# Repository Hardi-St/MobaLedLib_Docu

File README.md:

# MobaLedLib
Arduino library for controlling LEDs and other components on a model railway.

*****************************************************************
  This repository contains the documentation for the MobaLedLib
*****************************************************************

The use of RGB LEDs offers fascinating possibilities for lighting a model railway:
- Infinite number of lighting effects - Brightness and color of each LED can be
  set individually and dynamically
- Easiest cabling - The objects (houses, traffic lights, ...) are simply plugged
  into a multiple socket
- Extremely affordable - 100 LEDs for the price of three "normal" lights
- Up to 256 RGB LEDs (768 channels) can be controlled by an Arduino
- Controlling other components is just as easy
  - Sound modules
  - Servo and stepper motors
  - Power devices
- Additional module to read 80 and more switches with 10 signal wires
- Stand-alone operation or networked with other components possible

The lighting and some additional functions are controlled via the WS2812 / WS2811 chips.
For this, only a single signal is required which is forwarded from one chip to the next.
This makes the wiring extremely easy.

A lot of examples show the usage of the library. They could be use as startup for own programs.

This library is described in detail here:\
  https://www.stummiforum.de/viewtopic.php?f=7&t=165060&sid=e3b7f6122766c330d04cecf18b7b4878 \
Several videos which demonstrate the library are available in the following pages in the forum.

All forum pages are also available as PDF document:\
  http://www.thkas-moba.de/mobaled/MoBaLED_Stummi_Komplette_Seiten.pdf \
(The most recent pages may not be included)

Our wiki with all information can be found here: https://wiki.mobaledlib.de

You could also search for MobaLedLib in the internet.
\
\
Questions / suggestions / praise / ...
  MobaLedLib@gmx.de

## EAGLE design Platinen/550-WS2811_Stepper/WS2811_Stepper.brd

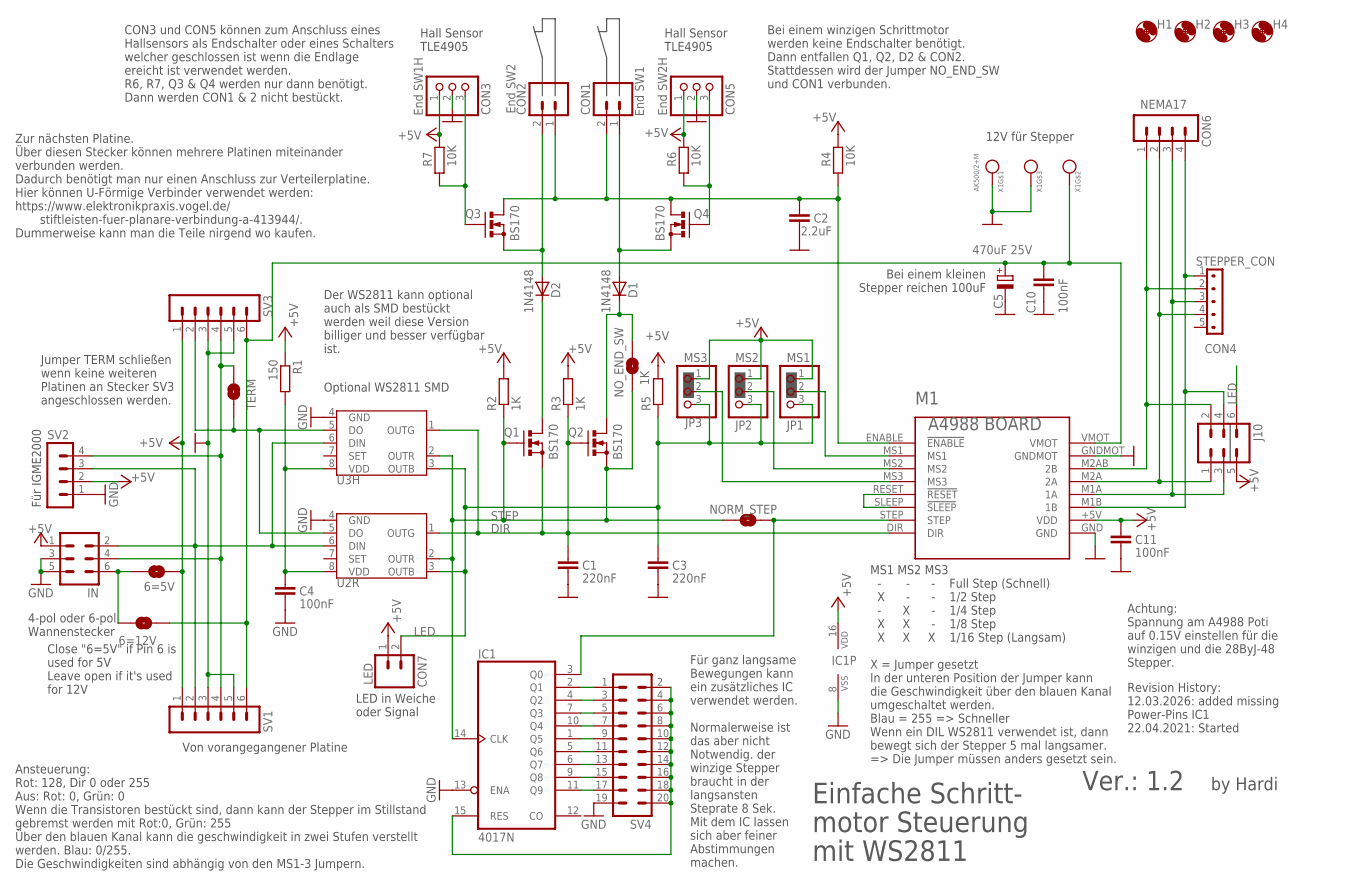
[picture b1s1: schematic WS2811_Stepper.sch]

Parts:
6=5V, 6=12V: SOLDERJUMPERNO; SJ_2S-NO
C1, C3: 220nF; C050-024X044
C2: 2.2uF; C050-024X044
C4, C10, C11: 100nF; C050-024X044
C5: 470uF 25V; E5-10,5
CON1: End SW1; 1X02
CON2: End SW2; 1X02
CON3: End SW1H; 1X03-CLEANBIG
CON4: STEPPER_CON
CON5: End SW2H; 1X03-CLEANBIG
CON6: NEMA17; MA04-1
CON7: LED; 1X02
D1, D2: 1N4148; DO35-7
H1, H2, H3, H4: MOUNT-HOLE2.0; 2,0
IC1: 4017N; DIL16
IN: ML6
J10: ML6
JP1: MS1; 1X03-CLEANBIG
JP2: MS2; 1X03-CLEANBIG
JP3: MS3; 1X03-CLEANBIG
M1: BOARD_A4988
NORM_STEP: SOLDERJUMPERNO; SJ_2S-NO
NO_END_SW: SOLDERJUMPERNO; SJ_2S-NO
Q1, Q2, Q3, Q4: BS170; SOT54E
R1: 150; RCL_0204/7
R2, R3, R5: 1K; RCL_0204/7
R4, R6, R7: 10K; RCL_0204/7
SV1, SV3: MA06-1
SV2: MA04-1
SV4: MA10-2
TERM: SOLDERJUMPERNO; SJ_2S-NO
U2R: WS2811; S3PO_MODUL_WS2811_SOUND_MP3-TF-16P_WS2811_AND_ATTINY_WS2811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
U3H: WS2811 SOT-8; SOP8
X1: AK500/2+M

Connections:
+5V: 6=5V.2, C11.1, CON3.1, CON5.1, CON7.1, IC1.16 (VDD), IN.1, J10.5, JP1.1, JP2.1, JP3.1, M1.+5V (VDD), R1.1, R2.2, R3.2, R4.2, R5.2, R6.2, R7.2, SV1.1, SV2.2, SV3.1
DIR: C1.1, M1.DIR, Q1.S, Q2.G, R3.1, U2R.1 (OUTG), U3H.1 (OUTG)
GND: C1.2, C2.2, C3.2, C4.2, C5.-, C10.2, C11.2, CON3.2, CON5.2, IC1.8 (VSS), IC1.13 (ENA), IN.3, IN.5, M1.GND, M1.GNDMOT, SV1.3, SV1.5, SV2.1, SV3.3, SV3.5, SV4.19, U2R.4 (GND), U3H.4 (GND), X1.1, X1.M
LED: C3.1, CON7.2, J10.6, JP1.3, JP2.3, JP3.3, R5.1, U2R.3 (OUTB), U3H.3 (OUTB)
M1A: CON4.3, CON6.3, J10.3, M1.M1A (1A)
M1B: CON4.1, CON6.4, J10.4, M1.M1B (1B)
M2A: CON4.4, CON6.2, J10.1, M1.M2A (2A)
M2B: CON4.2, CON6.1, J10.2, M1.M2AB (2B)
unnamed: M1.RESET (!RESET), M1.SLEEP (!SLEEP)
unnamed: IN.2, SV1.2, SV2.3, U2R.6 (DIN), U3H.6 (DIN)
unnamed: SV3.2, TERM.2, U2R.5 (DO), U3H.5 (DO)
unnamed: IN.4, SV1.4, SV2.4, SV3.4, TERM.1
unnamed: C4.1, R1.2, U2R.8 (VDD), U3H.8 (VDD)
unnamed: C2.1, CON1.2, CON2.1, M1.ENABLE (!ENABLE), Q3.D, Q4.D, R4.1
unnamed: CON1.1, D1.A, Q4.S
unnamed: CON2.2, D2.A, Q3.S
unnamed: CON5.3, Q4.G, R6.1
unnamed: D2.C, Q1.D
unnamed: D1.C, NO_END_SW.1, Q2.D
unnamed: JP2.2, M1.MS2
unnamed: 6=5V.1, 6=12V.2, IN.6
unnamed: CON3.3, Q3.G, R7.1
unnamed: IC1.2 (Q1), SV4.1
unnamed: IC1.4 (Q2), SV4.3
unnamed: IC1.7 (Q3), SV4.5
unnamed: IC1.10 (Q4), SV4.7
unnamed: JP1.2, M1.MS1
unnamed: IC1.1 (Q5), SV4.9
unnamed: IC1.5 (Q6), SV4.11
unnamed: IC1.6 (Q7), SV4.13
unnamed: IC1.9 (Q8), SV4.15
unnamed: JP3.2, M1.MS3
unnamed: IC1.11 (Q9), SV4.17
unnamed: IC1.15 (RES), SV4.2, SV4.4, SV4.6, SV4.8, SV4.10, SV4.12, SV4.14, SV4.16, SV4.18, SV4.20
unnamed: IC1.3 (Q0), M1.STEP, NORM_STEP.2
STEP: IC1.14 (CLK), NORM_STEP.1, NO_END_SW.2, Q1.G, Q2.S, R2.1, U2R.2 (OUTR), U3H.2 (OUTR)
VCC2: 6=12V.1, C5.+, C10.1, M1.VMOT, SV1.6, SV3.6, X1.2

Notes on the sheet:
4-pol oder 6-pol Wannenstecker
Close "6=5V" if Pin 6 is used for 5V Leave open if it's used for 12V
Optional WS2811 SMD
Zur nächsten Platine. Über diesen Stecker können mehrere Platinen miteinander verbunden werden. Dadurch benötigt man nur einen Anschluss zur Verteilerplatine. Hier können U-Förmige Verbinder verwendet werden: https://www.elektronikpraxis.vogel.de/ stiftleisten-fuer-planare-verbindung-a-413944/. Dum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
Von vorangegangener Platine
Der WS2811 kann optional auch als SMD bestückt werden weil diese Version billiger und besser verfügbar ist.
Jumper TERM schließen wenn keine weiteren Platinen an Stecker SV3 angeschlossen werden.
Revision History: 12.03.2026: added missing Power-Pins IC1 22.04.2021: Started
MS1 MS2 MS3 - - - Full Step (Schnell) X - - 1/2 Step - X - 1/4 Step X X - 1/8 Step X X X 1/16 Step (Langsam) X = Jumper gesetzt In der unteren Position der Jumper kann die Geschwindigkeit über den blauen Kanal umgeschaltet werden. Blau = 255 => Schneller Wenn ein DIL WS2811 verwendet ist, dann bewe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
12V für Stepper
by Hardi
Ver.: 1.2
Einfache Schritt- motor Steuerung mit WS2811
Bei einem winzigen Schrittmotor werden keine Endschalter benötigt. Dann entfallen Q1, Q2, D2 & CON2. Stattdessen wird der Jumper NO_END_SW und CON1 verbunden.
Achtung: Spannung am A4988 Poti auf 0.15V einstellen für die winzigen und die 28ByJ-48 Stepper.
Ansteuerung: Rot: 128, Dir 0 oder 255 Aus: Rot: 0, Grün: 0 Wenn die Transistoren bestückt sind, dann kann der Stepper im Stillstand gebremst werden mit Rot:0, Grün: 255 Über den blauen Kanal kann die geschwindigkeit in zwei Stufen verstellt werden. Blau: 0/255. Die Geschwindigkeiten sind abhängig v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
Hall Sensor TLE4905
CON3 und CON5 können zum Anschluss eines Hallsensors als Endschalter oder eines Schalters welcher geschlossen ist wenn die Endlage ereicht ist verwendet werden. R6, R7, Q3 & Q4 werden nur dann benötigt. Dann werden CON1 & 2 nicht bestückt.
Für IGME2000
Für ganz langsame Bewegungen kann ein zusätzliches IC verwendet werden. Normalerweise ist das aber nicht Notwendig. der winzige Stepper braucht in der langsansten Steprate 8 Sek. Mit dem IC lassen sich aber feiner Abstimmungen machen.
LED in Weiche oder Signal
Bei einem kleinen Stepper reichen 100uF

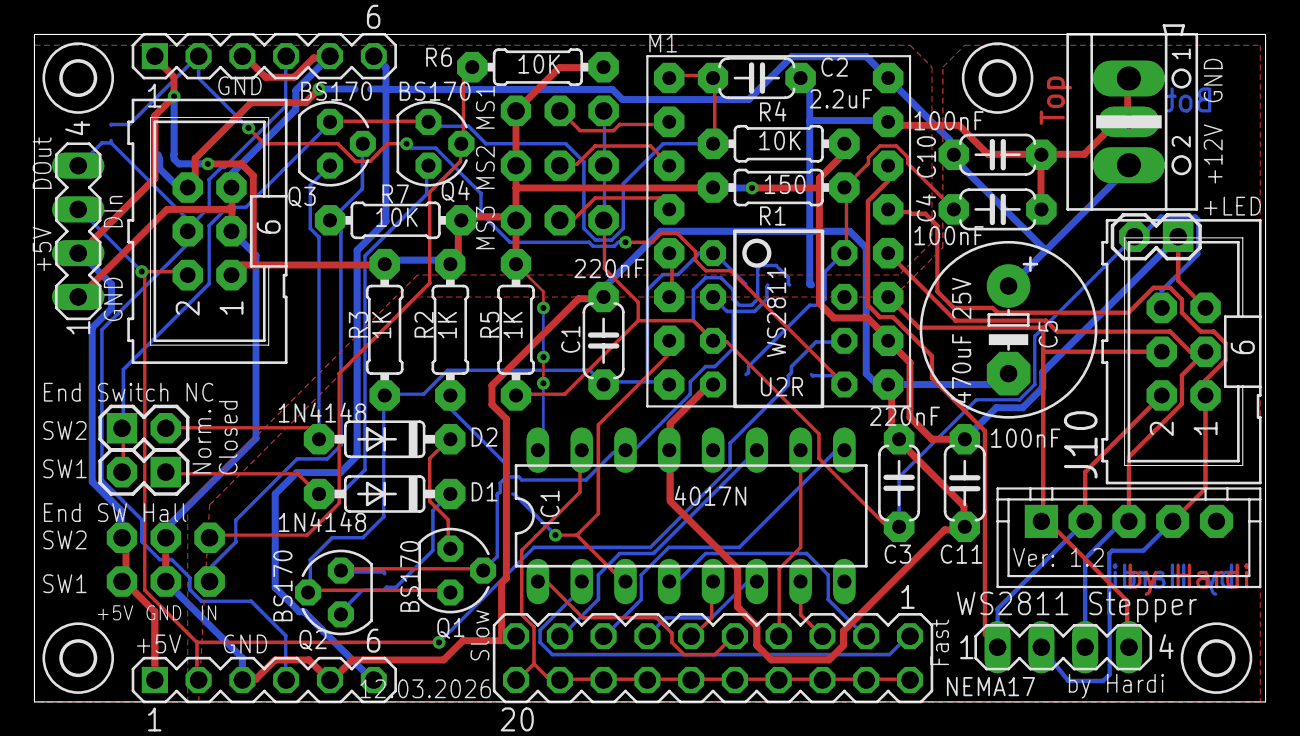
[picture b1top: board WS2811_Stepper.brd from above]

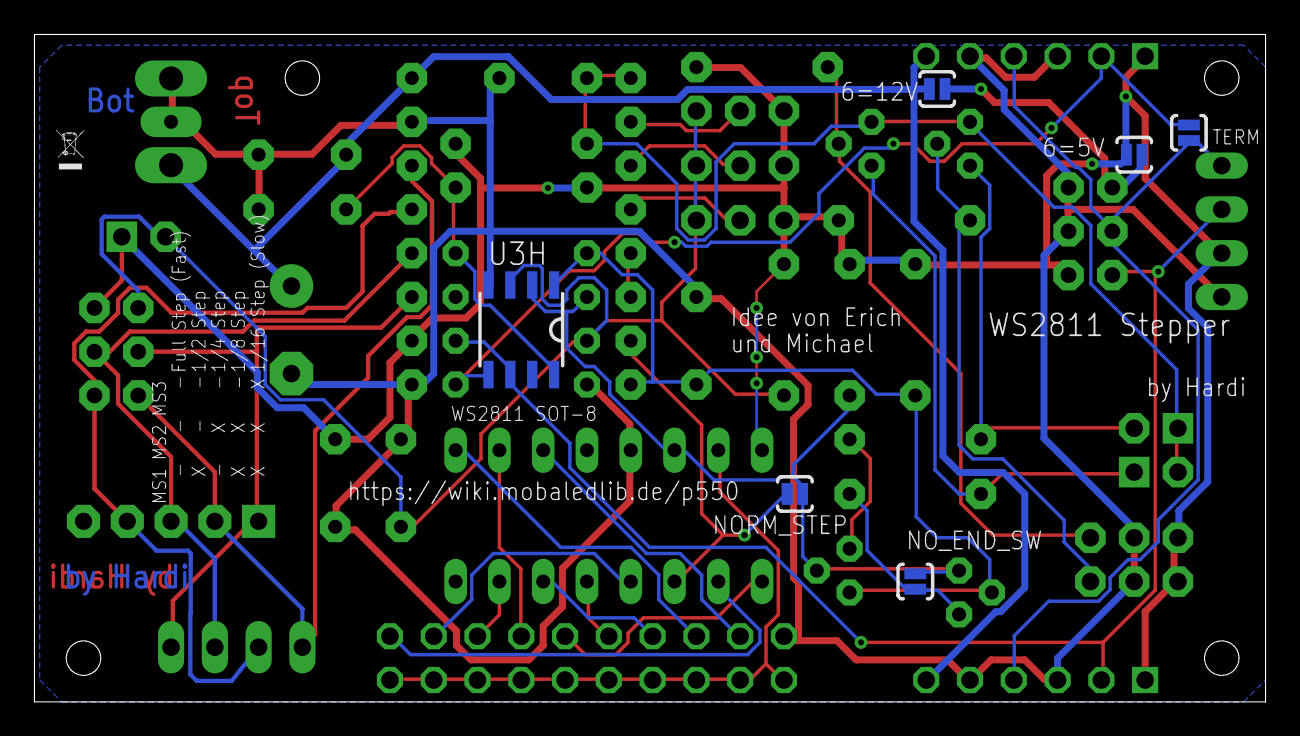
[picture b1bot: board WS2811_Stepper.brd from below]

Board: 2 copper layers, 71.4 x 38.7 mm, 50 parts (6 on the bottom side), 37 nets.

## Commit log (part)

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2023-12-06 Corretion Board-Number
2023-12-06 Delete Platinen/von_Theo/MLL_Connect/MLL_Connect_v10.zip
    Wrong file names into .zip
2023-12-06 Wrong file names into .zip
2023-12-06 Delete Platinen/von_Theo/MLL_Connect/MLL_Connect_v10_18x_VCut.zip
    Changed position CON3 (turn 180)
2023-12-06 Changed position CON3 (turn 180)
2023-12-09 Release Version 3.2.1j
2023-12-21 ATTinyCore package added
2023-12-26 Create Gehaeuse-522_Multi-Extender
2023-12-31 add images
2023-12-31 update images
2023-12-31 Update Layout
2024-01-20 Release Version 3.3.2a
2024-03-12 Release Version 3.3.2b
2024-03-27 add openSCAD source files
2024-03-28 Einrichtung Wagon
2024-03-29 Rename Stepper Unterflur V4.zip to Stepper Unterflur V4 Quelldateien passwortgeschützt.zip
2024-04-17 Gerber MLL Hauptplatine v3.3
2024-05-30 Update Bestueckungsanleitungen
    Unterstützung der 5V Versorgung über die Moba-Zentralen entfernt
2024-09-09 Platine 211 hinzugefuegt
2024-09-19 Schaltplaene aktualisert
2024-09-19 Schaltplaene aktualisert - Welle 2
2024-09-23 Beta 3.3.2C: Corrected Selectrix for ESP32
2024-11-28 add a copy of http://drazzy.com/package_drazzy.com_index.json
2024-11-28 fork files from https://azduino.com/bin/micronucleus/
2024-11-28 change urls to forked files
2024-11-28 fix filename
2024-12-13 Release Version 3.3.2d
2024-12-27 Release Version 3.3.2e
2025-01-11 Rename 38ca3a.stl to MLL_LED_Matrix_8x8.stl
2025-01-11 Rename 396a4b.stl to MLL_RGB_Push_Button_Platine.stl
2025-01-11 Rename 832f0a.stl to MLL_Verteilerplatine_200.stl
2025-01-11 Rename 92a0a0.stl to MLL_Sound_Modul_MP3-TF-16P.stl
2025-01-11 Rename 9bcb39.stl to 4er_Relais_Platine.stl
2025-01-11 Rename ac8397.stl to MLL_Mini_Verteiler.stl
2025-01-11 Rename bd918d.stl to MLL_Hauptplatine_101_1.8.2.stl
2025-01-11 Rename bf21ce.stl to MLL_Servo_Platine.stl
2025-02-09 Warnung 4KHz
    Warnhinweis fuer die WS2811 mit 4KHz hinzugefuegt
2025-02-12 Anleitungen 510de aktualisiert
2025-03-06 fits WS2811-Module S009A
2025-03-28 Trennung Versionen der Platine
2025-04-22 Release Version 3.3.2g
2025-04-24 add copy of index with 'wrong' filename
2025-04-25 Release Version 3.4.0
2025-05-20 Platinen für Roco Lollo (DC Umbau auf AC) und Roco V80 (AC oder DC Sound) hinzugefügt
2025-05-20 Neue Layouts für die Gleissperrsignale
2025-05-20 E32 Platinen hinzugefügt
2025-05-20 Ee33 Platinen hinzugefügt
2025-05-20 Platinen für 20mm Schallkapsel hinzugefügt
2025-05-21 Platinen für BR86 hinzugefügt
2025-05-29 Release Version 3.4.0a
2025-06-04 V100 Platinen
2025-06-04 V100 Korrektur
2025-06-20 Release Version 3.4.0b
2025-06-21 Release Version 3.4.0b2
2025-07-28 Release Version 3.4.0c
2025-08-12 Building instructions corrected
    ~ Thanks FSCHUM for reporting the error with the WS2811 ICs and the specification 400MHZ, correct is 400Hz
2025-09-06 Update ACS712-Display
    ~ ACS712-Display.ino
    add support of 16 WS2812B (8 on Mainboard, 8 on Childboard)
2025-09-10 Instructions updated
    ~ Links to the shop updated
    ~ PDF naming convention adjusted
2025-10-05 Anpassung WS2811
2025-10-31 Release 3.4.0c2
2025-11-02 Release Version 3.4.0D
2025-11-28 Release Version 3.5.0C
2025-12-04 Release Version 3.5.0C1
2026-01-26 Add files via upload
    Einstellbares Blaulicht ähnlich Bluelight1 MLL
2026-01-26 Einstellbares Blaulicht ähnlich Bluelight1 MLL
2026-01-26 Einstellbares Blaulicht ähnlich Bluelight2 MLL
2026-01-26 Drehendes Blaulicht mit 4 LEDs - 28ms links
2026-01-26 Drehendes Blaulicht mit 4 LEDs - 32ms rechts
2026-01-26 Drehendes Blaulicht mit zweimal 4 LEDs versetzt
2026-02-07 Delete Platinen/von_Theo/MLL_Stepper/MLL_Stepper_v11-[MLL_Stepper_v1.1].zip
    Filenames cannot contain special characters or the following words
2026-02-07 Delete Platinen/von_Theo/MLL_Stepper/MLL_Stepper_v11-[(6x) V-Cut].zip
    Filenames cannot contain special characters or the following words
2026-02-07 Add files via upload
    Old filename was not correct for manufacturing (Filenames cannot contain special characters)
2026-03-07 Aktualsierung der Bestückungsanleitungen
2026-03-12 added missing Power-Pins IC1
    added missing Power-Pins IC1
2026-03-12 added missing Power-Pins IC1
2026-03-13 Release Version 3.5.0F
2026-03-13 Release 3.5.0F1
2026-03-19 add workflow
2026-03-19 add test firmware
2026-03-19 update workflow
2026-03-19 move script to right directory
2026-03-19 move script to correct folder
2026-03-19 change script location
2026-03-19 fix script
2026-03-19 Automatically: Update firmware/index.json
2026-03-19 improve script
2026-03-19 add servo test firmware
2026-03-19 update scripts
2026-03-19 remove firmware
2026-03-19 update yml to do full checkout
2026-03-19 use sparse checkout
2026-03-19 add a corrupt test file
2026-03-19 try cone mode again
2026-03-19 found wrong folder name
2026-03-19 correct scripts
2026-03-19 add beta firmware files
2026-03-19 improve firmware file format
2026-03-23 Release 3.5.0G
2026-03-26 range change to 10-210 improved servo initialization and logging
2026-03-26 add version 0.6, restore original 0.5
2026-04-09 Add files via upload
    Geringe Auflösung der Bilder und ohne Video
2026-04-10 remove obsolete files
2026-04-10 add readme for deploying a beta version
2026-04-10 change to .md format to allow better formatting
2026-04-10 Update beta release steps in documentation
2026-04-11 Release 3.5.0H
2026-04-11 fix typo
2026-05-01 add servo version 0.7 fixing the twitch issue
2026-05-09 zusaetzliche Gehaeuse fuer die ESP32-Erweiterung
    Danke fuer die Files
    https://forum.mobaledlib.de/viewtopic.php?t=867#p7540
2026-05-13 Release 3.5.0I

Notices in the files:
parts and their libraries:
SparkFun-Retired: Licensing:Creative Commons ShareAlike 4.0 International - https://creativecommons.org/licenses/by-sa/4.0
